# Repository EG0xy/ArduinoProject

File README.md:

# ArduinoProject

My Codes for my Arduino Projects

Free to anyone

Have fun with it

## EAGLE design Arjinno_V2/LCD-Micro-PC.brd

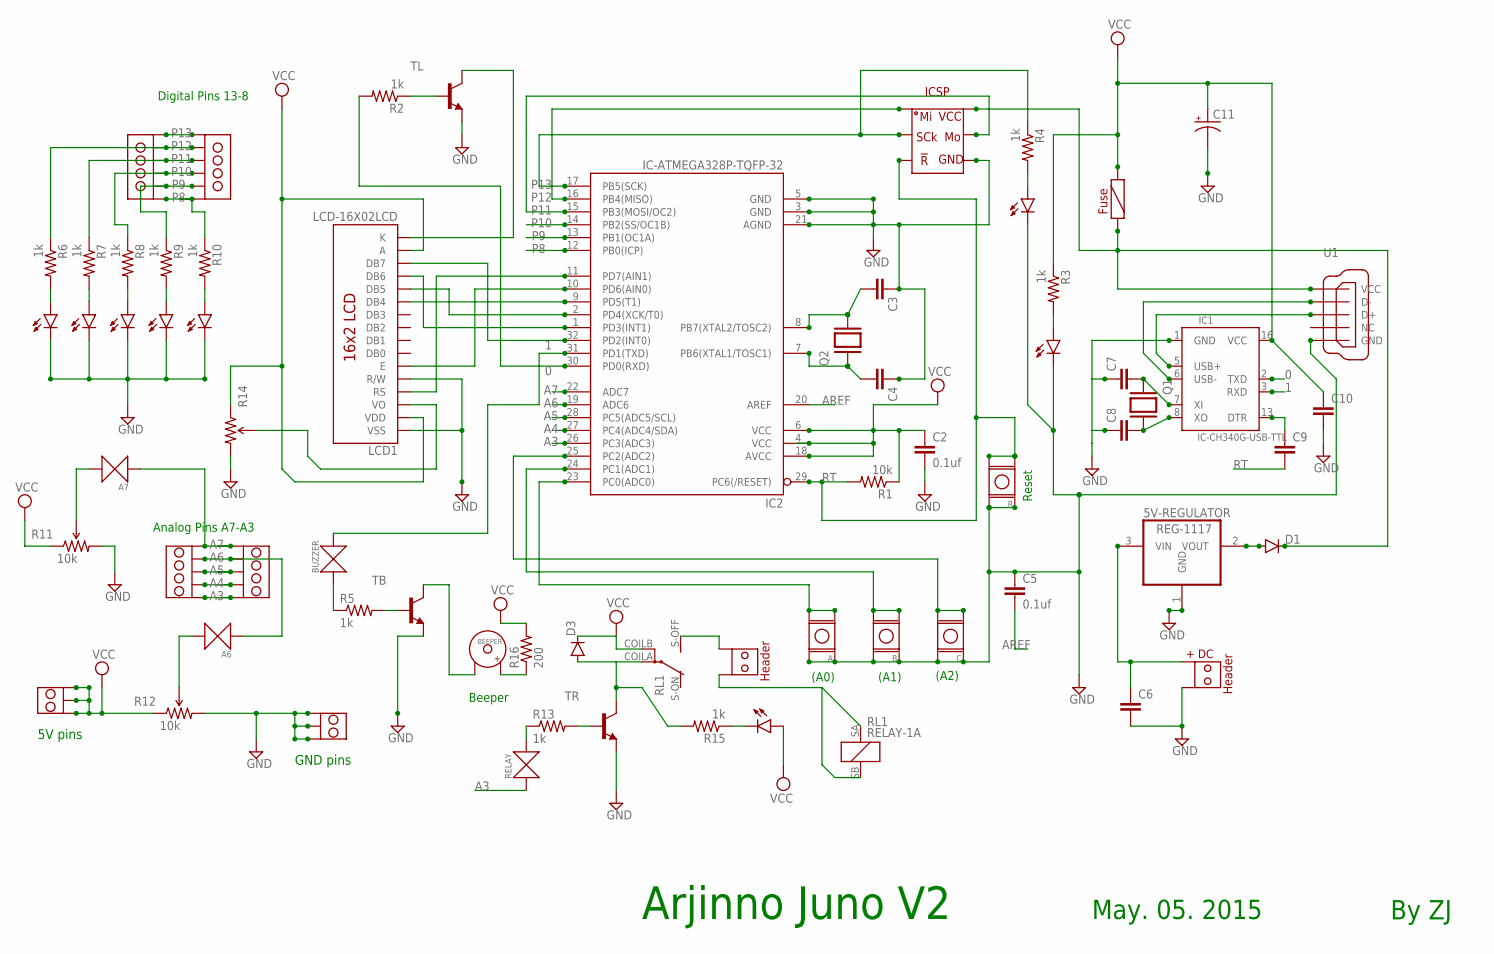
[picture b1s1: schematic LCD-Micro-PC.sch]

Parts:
5V-REGULATOR: REG-1117; SOT-223@1
A: BUTTON-6X6; BUT-6X6
A6, A7: TRACE-0.6MM; TRACE
B: BUTTON-6X6; BUT-6X6
BEEPER: BUZZER-12MM; BUZ-12MM
BUZZER: TRACE-0.6MM; TRACE
C: BUTTON-6X6; BUT-6X6
C2, C5: 0.1uf; 0805
C3, C4, C6: CAP-0805; 0805
C7, C8, C9, C10: CAP-SMD-0805; 0805
C11: CAP-POL-6MM-SMD; CAP-POL-6.3X7.7MM
D1: DIODE-SMA-4MM; DIODE-SMA
D3: DIODE-SOD-1206; SOD-1206
FUSE: FUSE; 0805
GND: HEADER-3P
H1: HEADER-2P
IC1: IC-CH340G-USB-TTL; SOP-16
IC2: IC-ATMEGA328P-TQFP-32; TQFP32-08MM
LCD1: LCD-16X02LCD; LCD-1602
LED1, LED3, LED4, LED6, LED7, LED8, LED9, LED10: LED-0805
Q1, Q2: CRYSTAL-5032
R: BUTTON-4X4-SMD; BUT-SMD-4X4
R1: 10k; 0805
R2, R3, R4, R5, R6, R7, R8, R9, R10, R13, R15: 1k; 0805
R11: 10k; POT-5X5MM@1
R12: 10k; POT-10X10MM@1
R14: POTENTIOMETER-3MM-SMD; POT-3MM-SMD
R16: 200; 0805
RELAY: TRACE-0.6MM; TRACE
RL1: RELAY-1A; REL-G5V1
TB: NPN-S8050-J3Y-0.3W; SOT-23
TL: NPN-S8050-J3Y-0.3W; SOT-23
TR: NPN-S8050-J3Y-0.3W; SOT-23
U1: USB-MINI
U$1: ISCP-6PINS; ISCP
U$2: HEADER-2P-DC
U$9, U$12: HEADER-5P
U$10, U$11: HEADER-6P
VCC: HEADER-3P

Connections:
0: IC1.2 (TXD), IC2.30 (PD0(RXD)), R2.2
1: BUZZER.P$2, IC1.3 (RXD), IC2.31 (PD1(TXD))
A3: IC2.26 (PC3(ADC3)), RELAY.P$1, U$9.P$5, U$12.P$1
A4: IC2.27 (PC4(ADC4/SDA)), U$9.P$4, U$12.P$2
A5: IC2.28 (PC5(ADC5/SCL)), U$9.P$3, U$12.P$3
A6: A6.P$1, IC2.19 (ADC6), U$9.P$2, U$12.P$4
A7: A7.P$1, IC2.22 (ADC7), U$9.P$1, U$12.P$5
AREF: C5.2, IC2.20 (AREF)
GND: 5V-REGULATOR.1 (GND), A.B0, A.B1, B.B0, B.B1, C.B0, C.B1, C2.2, C3.1, C4.1, C5.1, C6.2, C7.1, C8.1, C10.2, C11.-, GND.P$1, GND.P$2, GND.P$3, IC1.1 (GND), IC2.3 (GND), IC2.5 (GND), IC2.21 (AGND), LCD1.1 (VSS), LCD1.5 (R/W), LED3.C, LED4.C, LED6.C, LED7.C, LED8.C, LED9.C, LED10.C, R.B1 (B0), R.B2 (B1), R11.3 (CW), R12.3 (CW), R14.3 (CW), TB.2 (E), TL.2 (E), TR.2 (E), U1.5 (GND), U$1.P$4, U$2.-
unnamed: IC2.32 (PD2(INT0)), LCD1.14 (DB7)
unnamed: IC2.1 (PD3(INT1)), LCD1.13 (DB6)
unnamed: IC2.2 (PD4(XCK/T0)), LCD1.12 (DB5)
unnamed: IC2.9 (PD5(T1)), LCD1.11 (DB4)
unnamed: LCD1.16 (K), TL.3 (C)
unnamed: BUZZER.P$1, R5.1
unnamed: R2.1, TL.1 (B)
unnamed: IC1.5 (USB+), U1.3 (D+)
unnamed: LCD1.3 (VO), R14.2 (WIPER)
unnamed: IC2.10 (PD6(AIN0)), LCD1.6 (E)
unnamed: IC2.11 (PD7(AIN1)), LCD1.4 (RS)
unnamed: A.A0, A.A1, IC2.23 (PC0(ADC0))
unnamed: B.A0, B.A1, IC2.24 (PC1(ADC1))
unnamed: C.A0, C.A1, IC2.25 (PC2(ADC2))
unnamed: LED3.A, R3.2
unnamed: BEEPER.-, TB.3 (C)
unnamed: LED1.C, R15.1
unnamed: LED6.A, R6.2
unnamed: LED7.A, R7.2
unnamed: LED4.A, R4.2
unnamed: LED8.A, R8.2
unnamed: LED9.A, R9.2
unnamed: R5.2, TB.1 (B)
unnamed: LED10.A, R10.2
unnamed: C3.2, IC2.8 (PB7(XTAL2/TOSC2)), Q2.2
unnamed: C4.2, IC2.7 (PB6(XTAL1/TOSC1)), Q2.1
unnamed: 5V-REGULATOR.2 (VOUT), D1.A
unnamed: A7.P$2, R11.2 (WIPER)
unnamed: D3.A, R15.2, RL1.COILA, TR.3 (C)
unnamed: 5V-REGULATOR.3 (VIN), C6.1, U$2.+
unnamed: H1.P$2 (-), RL1.SA (1), RL1.SB (2)
unnamed: A6.P$2, R12.2 (WIPER)
unnamed: H1.P$1 (+), RL1.S-OFF (SW)
unnamed: D1.C, FUSE.1, U1.1 (VCC), U$1.P$6
unnamed: R13.2, TR.1 (B)
unnamed: IC1.6 (USB-), U1.2 (D-)
unnamed: C7.2, IC1.7 (XI), Q1.1
unnamed: C8.2, IC1.8 (XO), Q1.2
unnamed: C9.1, IC1.13 (DTR)
unnamed: BEEPER.+, R16.1
unnamed: R13.1, RELAY.P$2
P8: IC2.12 (PB0(ICP)), R10.1, U$10.P$6, U$11.P$1
P9: IC2.13 (PB1(OC1A)), R9.1, U$10.P$5, U$11.P$2
P10: IC2.14 (PB2(SS/OC1B)), R8.1, U$10.P$4, U$11.P$3
P11: IC2.15 (PB3(MOSI/OC2)), R7.1, U$1.P$5, U$10.P$3, U$11.P$4
P12: IC2.16 (PB4(MISO)), R6.1, U$1.P$1, U$10.P$2, U$11.P$5
P13: IC2.17 (PB5(SCK)), R4.1, U$1.P$2, U$10.P$1, U$11.P$6
RT: C9.2, IC2.29 (PC6(/RESET)), R.A0, R.A1, R1.2, U$1.P$3
VCC: C2.1, C10.1, C11.+, D3.C, FUSE.2, IC1.16 (VCC), IC2.4 (VCC), IC2.6 (VCC), IC2.18 (AVCC), LCD1.2 (VDD), LCD1.15 (A), LED1.A, R1.1, R3.1, R11.1 (CCW), R12.1 (CCW), R14.1 (CCW), R16.2, RL1.COILB, VCC.P$1, VCC.P$2, VCC.P$3

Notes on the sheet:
May. 05. 2015
(A0)
(A1)
(A2)
Reset
Digital Pins 13-8
Analog Pins A7-A3
Beeper
By ZJ
Arjinno Juno V2
5V pins
GND pins

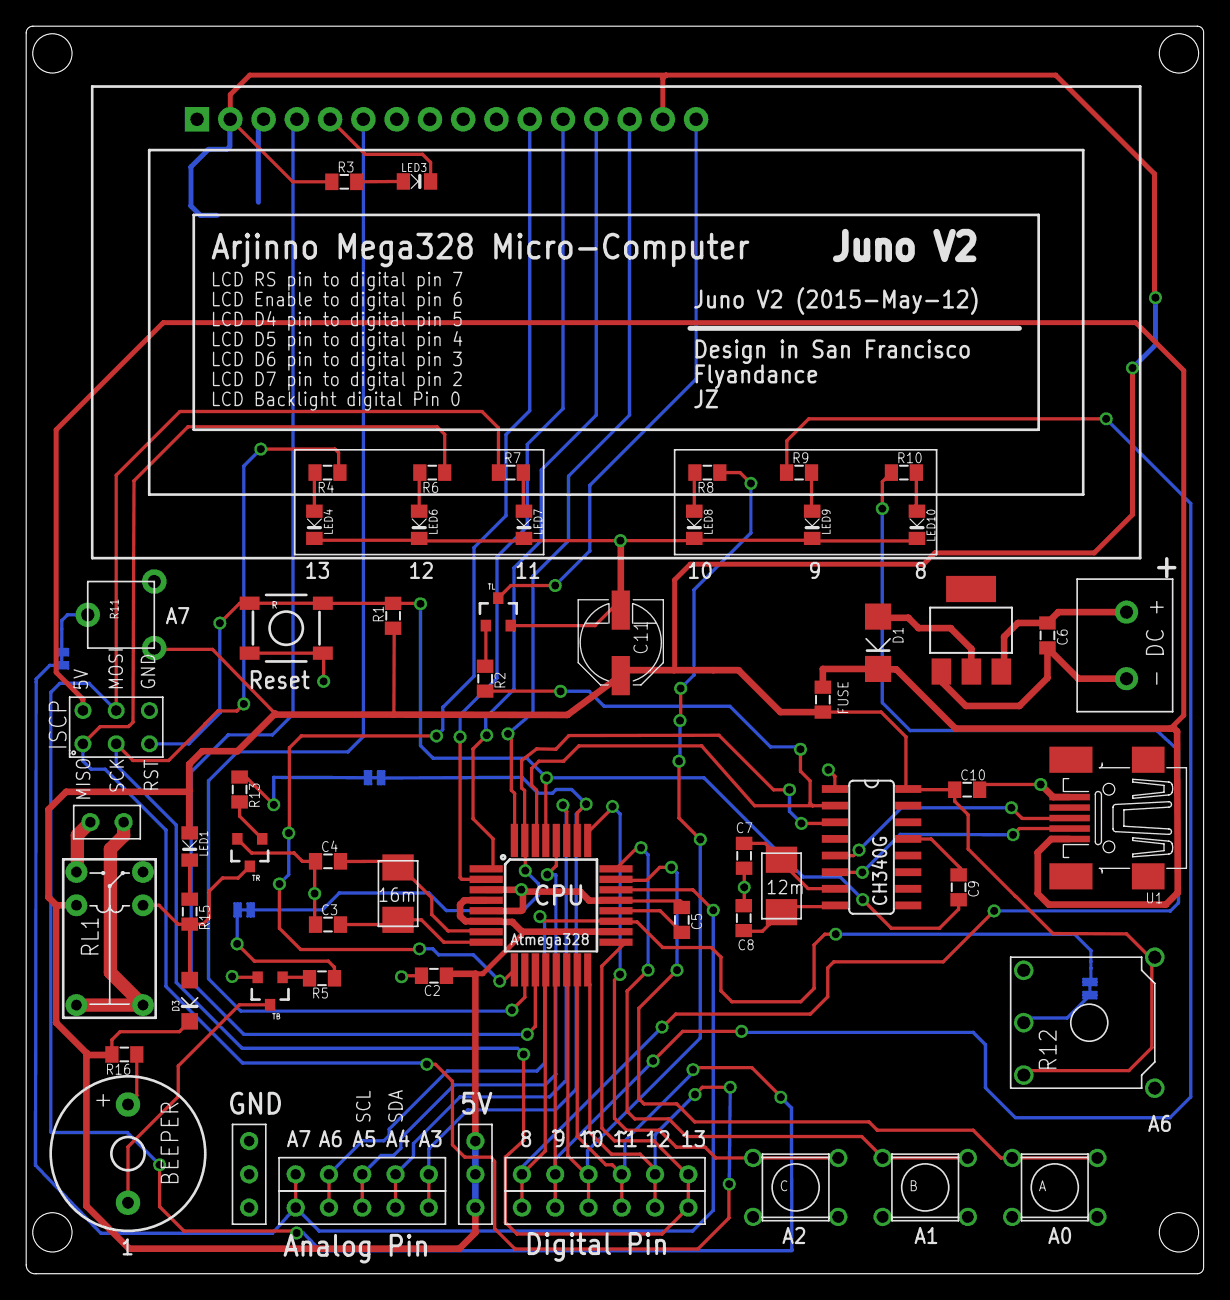
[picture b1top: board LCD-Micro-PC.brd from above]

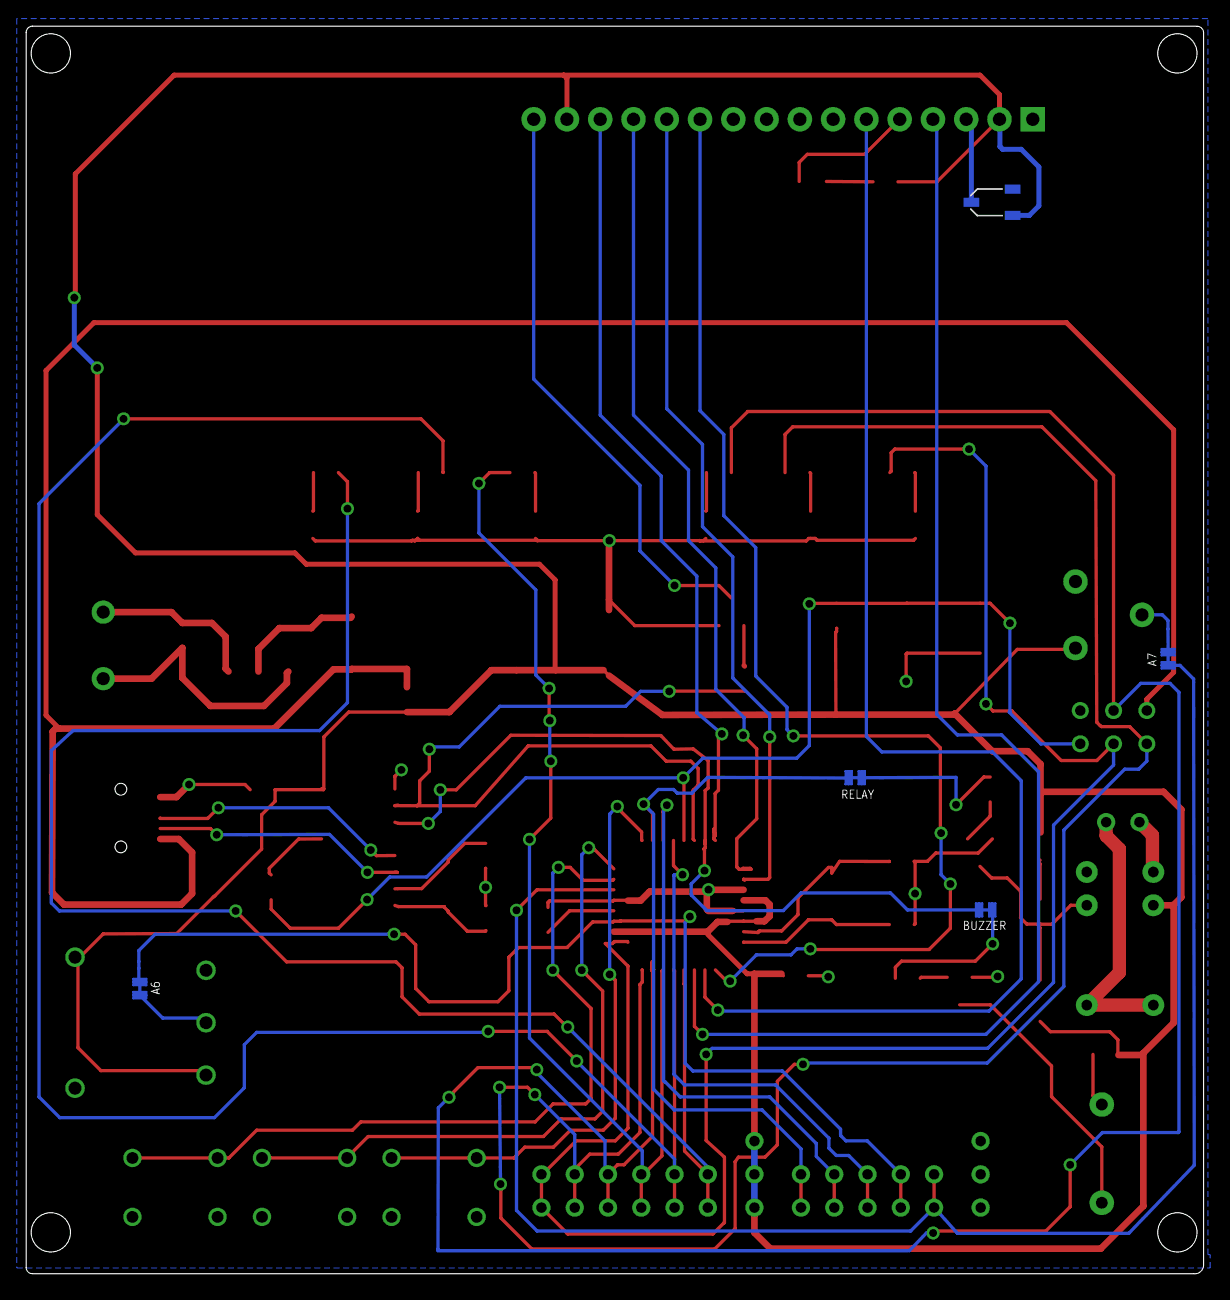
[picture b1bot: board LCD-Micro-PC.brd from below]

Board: 2 copper layers, 89.9 x 95.2 mm, 66 parts (5 on the bottom side), 58 nets.

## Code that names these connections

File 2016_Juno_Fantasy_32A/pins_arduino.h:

#ifndef Pins_Arduino_h
#define Pins_Arduino_h

#include <avr/pgmspace.h>
/*
ATmega32
   
PCINT15-8: D7-0  : bit 1
PCINT31-24: D15-8  : bit 3
PCINT23-16: D23-16 : bit 2
PCINT7-0: D31-24   : bit 0
*/

#define STANDARD_PINOUT
#define NUM_DIGITAL_PINS            32
#define NUM_ANALOG_INPUTS           8
#define analogInputToDigitalPin(p)  ((p < NUM_ANALOG_INPUTS) ? (p) + 24 : -1)
#define digitalPinToInterrupt(p)  ((p) == 2 ? 2 : ((p) == 10 ? 0 : ((p) == 11 ? 1 : NOT_AN_INTERRUPT)))

#if defined(__AVR_ATmega8535__) || defined(__AVR_ATmega16__) || defined(__AVR_ATmega32__)
#define digitalPinHasPWM(p)         ((p) == 3 || (p) == 12 || (p) == 13 || (p) == 15)

#elif defined(__AVR_ATmega164A__) || defined(__AVR_ATmega164P__) || defined(__AVR_ATmega324A__) || \
defined(__AVR_ATmega324P__) || defined(__AVR_ATmega324PA__) || defined(__AVR_ATmega644__) || \
defined(__AVR_ATmega644P__)
#define digitalPinHasPWM(p)         ((p) == 3 || (p) == 4 || (p) == 12 || (p) == 13 || (p) == 14 || (p) == 15)

#elif defined(__AVR_ATmega1284__) || defined(__AVR_ATmega1284P__)
 #define digitalPinHasPWM(p)         ((p) == 3 || (p) == 4 || (p) == 6 || (p) == 7 || (p) == 12 || (p) == 13 || (p) == 14 || (p) == 15)
#endif


static const uint8_t LED = 15;
#define LED_BUILTIN 0

static const uint8_t SS   = 12;
static const uint8_t MOSI = 13;
static const uint8_t MISO = 14;
static const uint8_t SCK  = 15;

static const uint8_t SDA = 17;
static const uint8_t SCL = 16;

static const uint8_t A0 = 0;
static const uint8_t A1 = 1;
static const uint8_t A2 = 2;
static const uint8_t A3 = 3;
static const uint8_t A4 = 4;
static const uint8_t A5 = 5;
static const uint8_t A6 = 6;
static const uint8_t A7 = 7;


#if defined(__AVR_ATmega164A__) || defined(__AVR_ATmega164P__) || defined(__AVR_ATmega324A__) || \
defined(__AVR_ATmega324P__) || defined(__AVR_ATmega324PA__) || defined(__AVR_ATmega644__) || \
defined(__AVR_ATmega644P__) || defined(__AVR_ATmega1284__) || defined(__AVR_ATmega1284P__)
#define digitalPinToPCICR(p)    (((p) >= 0 && (p) < NUM_DIGITAL_PINS) ? (&PCICR) : ((uint8_t *)0))
#define digitalPinToPCICRbit(p) (((p) <= 7) ? 1 : (((p) <= 15) ? 3 : (((p) <= 23) ? 2 : 0)))
#define digitalPinToPCMSK(p)    (((p) <= 7) ? (&PCMSK2) : (((p) <= 13) ? (&PCMSK0) : (((p) <= 21) ? (&PCMSK1) : ((uint8_t *)0))))
#define digitalPinToPCMSKbit(p) ((p) % 8)
#endif

#if defined(__AVR_ATmega164A__) || defined(__AVR_ATmega164P__) || defined(__AVR_ATmega324A__) || \
defined(__AVR_ATmega324P__) || defined(__AVR_ATmega324PA__)
/**** Needed to get the SD library to work. 
Missing definitions in the iom164.h/iom324.h file ****/
#define SPR0 0
#define SPR1 1
#define CPHA 2
#define CPOL 3
#define MSTR 4
#define DORD 5
#define SPE 6
#define SPIE 7
#define SPSR _SFR_IO8(0x2D)
#define SPI2X 0
#define WCOL 6
#define SPIF 7
#define SPCR _SFR_IO8(0x2C)
#define SPDR _SFR_IO8(0x2E)
#endif


#ifdef ARDUINO_MAIN

#define PA 1
#define PB 2
#define PC 3
#define PD 4

// these arrays map port names (e.g. port B) to the
// appropriate addresses for various functions (e.g. reading
// and writing)
const uint16_t PROGMEM port_to_mode_PGM[] =
{
	NOT_A_PORT,
	(uint16_t) &DDRA,
	(uint16_t) &DDRB,
	(uint16_t) &DDRC,
	(uint16_t) &DDRD,
};

const uint16_t PROGMEM port_to_output_PGM[] =
{
	NOT_A_PORT,
	(uint16_t) &PORTA,
	(uint16_t) &PORTB,
	(uint16_t) &PORTC,
	(uint16_t) &PORTD,
};

const uint16_t PROGMEM port_to_input_PGM[] =
{
	NOT_A_PORT,
	(uint16_t) &PINA,
	(uint16_t) &PINB,
	(uint16_t) &PINC,
	(uint16_t) &PIND,
};

const uint8_t PROGMEM digital_pin_to_port_PGM[] =
{
	PA,
	PA,
	PA,
	PA,
	PA,
	PA,
	PA,
	PA, 
	PB, 
	PB,
	PB,
	PB,
	PB,
	PB,
	PB,
	PB,
	PC,
	PC,
	PC,
	PC,
	PC,
	PC,
   	PC,
	PC,	
	PD,
	PD,
	PD,
	PD,
	PD,
	PD,
	PD,
	PD
};

const uint8_t PROGMEM digital_pin_to_bit_mask_PGM[] =
{
	_BV(0), /* D0, port A */
	_BV(1),
	_BV(2),
	_BV(3),
	_BV(4),
	_BV(5),
	_BV(6),
	_BV(7),
	_BV(0), /* D8, port B */
	_BV(1),
	_BV(2),
	_BV(3),
	_BV(4),
	_BV(5),
	_BV(6),
	_BV(7),
	_BV(0), /* D16, port C */
	_BV(1),
	_BV(2),
	_BV(3),
	_BV(4),
	_BV(5),
	_BV(6),
	_BV(7),
	_BV(0), /* D24, port D */
	_BV(1),
	_BV(2),
	_BV(3),
	_BV(4),
	_BV(5),
	_BV(6),
	_BV(7)
};


#if defined(__AVR_ATmega8535__) || defined(__AVR_ATmega16__) || defined(__AVR_ATmega32__)
const uint8_t PROGMEM digital_pin_to_timer_PGM[] =
{
	NOT_ON_TIMER, 	/* D0  - PA0 */
	NOT_ON_TIMER, 	/* D1  - PA1 */
	NOT_ON_TIMER, 	/* D2  - PA2 */
	NOT_ON_TIMER,   /* D3  - PA3 */
	NOT_ON_TIMER, 	/* D4  - PA4 */
	NOT_ON_TIMER, 	/* D5  - PA5 */
	NOT_ON_TIMER, 	/* D6  - PA6 */
	NOT_ON_TIMER,	/* D7  - PA7 */
	NOT_ON_TIMER, 	/* D8  - PB0 */
	NOT_ON_TIMER, 	/* D9  - PB1 */
	NOT_ON_TIMER, 	/* D10 - PB2 */
	TIMER0A, 	    /* D11 - PB3 */
	NOT_ON_TIMER,   /* D12 - PB4 */
	NOT_ON_TIMER,   /* D13 - PB5 */
	NOT_ON_TIMER,   /* D14 - PB6 */
	NOT_ON_TIMER,   /* D15 - PB7 */
	NOT_ON_TIMER, 	/* D16 - PC0 */
	NOT_ON_TIMER,   /* D17 - PC1 */
	NOT_ON_TIMER,   /* D18 - PC2 */
	NOT_ON_TIMER,   /* D19 - PC3 */
	NOT_ON_TIMER,   /* D20 - PC4 */
	NOT_ON_TIMER,   /* D21 - PC5 */
	NOT_ON_TIMER,   /* D22 - PC6 */
	NOT_ON_TIMER,   /* D23 - PC7 */
	NOT_ON_TIMER,   /* D24 - PD0 */
	NOT_ON_TIMER,   /* D25 - PD1 */
	NOT_ON_TIMER,   /* D26 - PD2 */
	NOT_ON_TIMER,   /* D27 - PD3 */
	TIMER1B,    	/* D28 - PD4 */
	TIMER1A,   		/* D29 - PD5 */
	NOT_ON_TIMER,   /* D30 - PD6 */
	TIMER2    		/* D31 - PD7 */
};


#endif // Timer defs

#endif // ARDUINO_MAIN

#endif // Pins_Arduino_h

// vim:ai:cin:sts=2 sw=2 ft=cpp

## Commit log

2015-01-18 Create Battery_Discharger_Test
2015-01-18 Update and rename Battery_Discharger_Test to Universal Battery Discharger
2015-01-18 Update Universal Battery Discharger
2015-01-18 KK
    KK
2015-01-19 library
2015-01-19 Create Codes for Arduino
2015-01-19 Create i2c_scanner
2015-01-19 Create i2cLCDguesser
2015-01-19 attiny
2015-01-19 Rename Codes for Arduino to code collections
2015-02-06 Create Accurate analog reading
2015-02-07 Create XCodes
2015-02-07 Update XCodes
2015-02-16 Create Universal Battery Discharger MarkII
2015-02-17 Update Universal Battery Discharger MarkII
2015-04-01 PCB
    PCB
2015-04-26 Create 7 segment led_multiplex
2015-04-26 Update 7 segment led_multiplex
2015-04-26 Update and rename 7 segment led_multiplex to 7 segment led_multiplex_74hc595
2015-04-26 Update 7 segment led_multiplex_74hc595
2015-05-07 Create Arjinno Juno V1 Test code
2015-05-09 Create Clock_wheel
2015-06-07 New
    New
2015-06-07 Create Code_Test
2015-06-08 Create Base_code
2015-06-08 Create Clock_test_code
2015-06-23 Create Universal Battery Discharger MarkIII
2015-06-23 Update Universal Battery Discharger MarkIII
2015-06-26 Create simple_clock_MarkII
2015-06-26 Create simple_clock
2015-07-09 s
    s
2015-07-09 Create Led_80_clock_M1
2015-07-09 Update Led_80_clock_M1
2015-07-13 Create Clock_mark_II
2015-07-26 led love
    led love
2015-07-26 hex
    hex
2015-09-16 Create Clock_Final
2015-09-18 Create LED_80_Clock_M2
2015-09-18 Update LED_80_Clock_M2
2015-09-18 Create LED_80_Clock_M3_F1
2015-09-19 Create Clock_74HC595_M4_F2
2015-09-19 Rename Clock_74HC595_M4_F2 to LED_80_Clock_M4_F2
2015-09-19 Create LED_80_Clock_M5_final
2015-09-22 Update LED_80_Clock_M5_final
2015-11-16 Create Juno_boost
2016-01-06 Create New
2016-01-10 update
    update
2016-01-10 code
    code
2016-02-03 Create Juno_mini_heart_mega
2016-02-03 Update Juno_mini_heart_mega
2016-03-23 Update and rename New.txt to 7-segment LED display example code
2016-03-23 Update and rename 7-segment LED display example code to 7-segment LED display example code
2016-03-23 Create 7-segment LED display example code_632 bytes
2016-03-23 Rename 7-segment LED display example code_632 bytes to 7-seg LED display_code_B
2016-03-23 Update and rename 7-segment LED display example code to 7-seg LED display_code_A
2016-03-23 Create 7-segment display code A
2016-03-23 Create 7-segment display code B
2016-03-23 Update 7-segment display code B
2016-04-06 Create New_Buff
2016-04-06 Rename New_Buff to ZNew
2016-04-06 Update ZNew
2016-04-08 Create Main_Button and_LED
2016-04-16 Create Code
2016-04-17 Update Code
2016-04-20 Create Pinouts_plus
2016-04-20 Update Pinouts_plus
2016-04-23 n
    n
2016-04-24 Create LED_Button_codes
2016-04-26 Create 7-seg-code
2016-04-27 Create 4_buttons_codes
2016-05-02 Create button_code
2016-05-02 Best analog and digital button library
2016-05-13 Rename Board_File_arduino_IDE_1.6.8 to Juno_Board_File_1.6.8
2016-05-14 Create clock_1
2016-05-14 Create clock_2
2016-05-29 Create 176uA_Version_2
2016-06-04 Create AVR_tricks
2016-06-04 Update AVR_tricks
2016-06-05 Create basic_80_led_control_code
2016-06-05 Update basic_80_led_control_code
2016-06-21 Create Juno_timer
2016-06-23 Create matrix_pro_clock
2016-07-12 Create Micro-PC V3 (Atmega8) I2C Slave
2016-07-12 Create Micro-PC V3 (Atmega328) I2C Master
2016-07-14 Update Micro-PC V3 (Atmega328) I2C Master
2016-07-14 Update Micro-PC V3 (Atmega8) I2C Slave
2016-07-16 Create Micro-PC V3 (Atmega328) Serial Master
2016-07-16 Create Arjinno_V3_Juno_micro_Micro-PC V3 (Atmega8) Serial Slave
2016-07-16 Rename Arjinno_V3_Juno_micro_Micro-PC V3 (Atmega8) Serial Slave to Arjinno_V3_Juno_micro_Micro-PC/Arjinno Micro-PC V3 (Atmega8) Serial Slave
2016-07-16 Create Micro-PC V3 (Atmega8) Serial Slave
2016-07-16 Update Micro-PC V3 (Atmega8) Serial Slave
2016-07-16 Update Micro-PC V3 (Atmega328) Serial Master
2016-07-20 Create Battery_Discharger_2016
2016-07-20 Update Battery_Discharger_2016
2016-09-02 fantasy
2016-09-02 Pin map
2016-09-02 core
2016-11-03 Create RX
2016-11-03 Create TX
